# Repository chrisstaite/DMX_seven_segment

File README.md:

# DMX Seven Segment
An implementation of a DMX controller using a seven segment display
on an ATmega32A.

This utilises a small board with three buttons for up/down/channel
and a seven segment display to show the value.  A WS2812 shows the
RGB value.

All of the code is written to be run directly on the ATmega32A
without any external libraries other than AVR-Libc.

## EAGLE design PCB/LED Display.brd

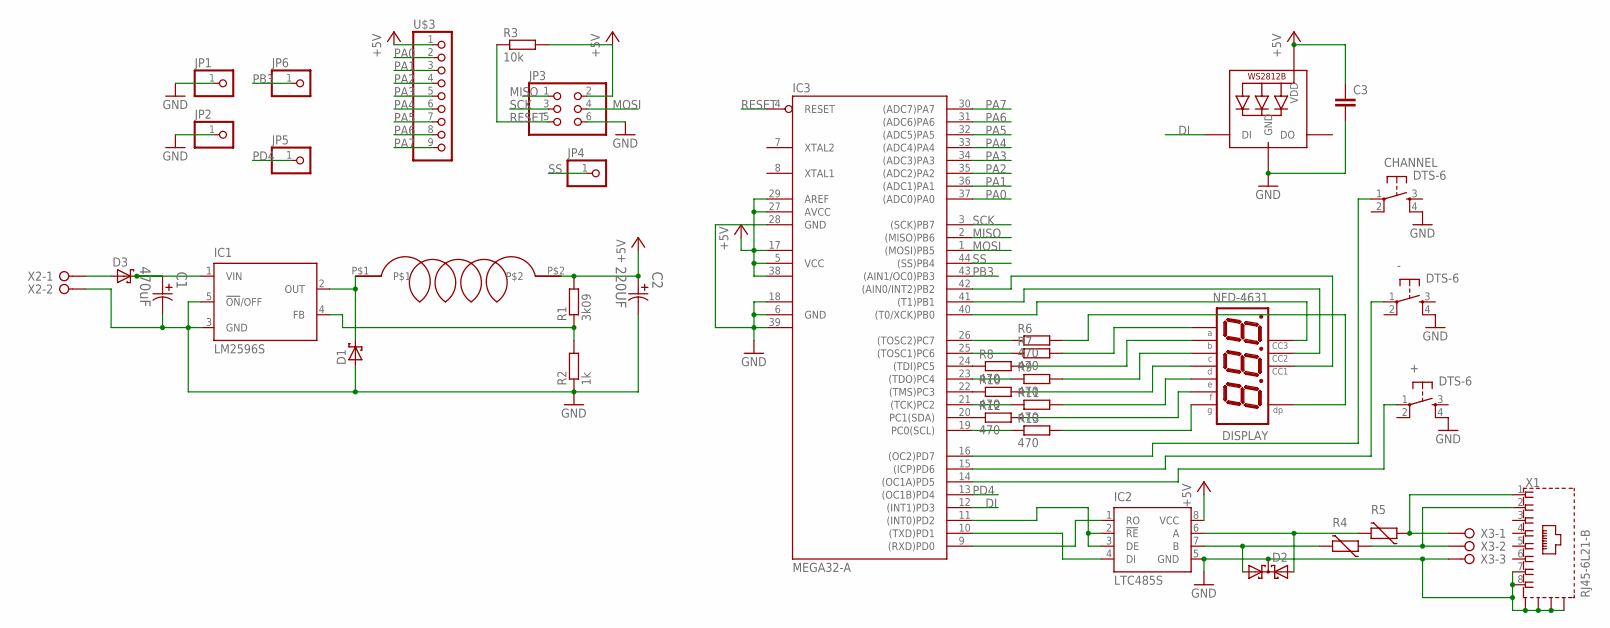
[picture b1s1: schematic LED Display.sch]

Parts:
+: DTS-6
-: DTS-6
C1: 470uF; CAPAE1030X1050N
C2: 220UF; CAPAE660X610N
C3: C-EUC0805; C0805
CHANNEL: DTS-6
D1, D3: MBRS130LT3; SMB
D2: BAS40-05; SOT23
DISPLAY: NFD-4631; NFD-5631
IC1: LM2596S; TO263-5
IC2: LTC485S; SOIC8
IC3: MEGA32-A; TQFP44
JP1, JP2, JP5, JP6: PINHD-1X1CB; 1X01-CLEANBIG
JP3: PINHD-2X3; 2X03
JP4: PINHD-1X1; 1X01
LED1: WS2812B5050; WS2812B
R1: 3k09; M0805
R2: 1k; M0805
R3: 10k; M0805
R4, R5: VARISTORCN1812; CT/CN1812; FARNELL 1652168
R6, R7, R8, R9, R10, R11, R12, R13: 470; M0805
U$1: SRN8040
U$3: PINHD-1X9; 1X09-BIG
X1: RJ45-6L21-B; RJ45-SHIELD1
X2: W237-02P; W237-132
X3: W237-03P; W237-133

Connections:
+5V: C2.1, C3.1, IC2.8 (VCC), IC3.5 (VCC), IC3.17 (VCC1), IC3.27 (AVCC), IC3.29 (AREF), IC3.38 (VCC2), JP3.2, LED1.1-VDD (VDD), R1.2, R3.2, U$1.P$2, U$3.1
DI: IC3.12 ((INT1)PD3), LED1.4-DIN (DI)
GND: +.4, -.4, C1.2, C2.2, C3.2, CHANNEL.4, D1.A, D2.3 (C), IC1.3 (GND), IC1.5 (!ON!/OFF), IC2.5 (GND), IC3.6 (GND), IC3.18 (GND1), IC3.28 (GND), IC3.39 (GND2), JP1.1, JP2.1, JP3.6, LED1.3-GND (GND), R2.1, X1.7, X1.8, X1.S1 (S), X1.S2 (S), X1.S3 (S), X1.S4 (S), X2.2, X3.3
MISO: IC3.2 ((MISO)PB6), JP3.1
MOSI: IC3.1 ((MOSI)PB5), JP3.4
unnamed: C1.1, D3.C, IC1.1 (VIN)
unnamed: D2.1 (A1), IC2.7 (B), R4.2
unnamed: IC1.4 (FB), R1.1, R2.2
unnamed: D1.C, IC1.2 (OUT), U$1.P$1
unnamed: D2.2 (A2), IC2.6 (A), R5.2
unnamed: IC2.2 (!RE), IC2.3 (DE), IC3.11 ((INT0)PD2)
unnamed: IC2.1 (RO), IC3.9 ((RXD)PD0)
unnamed: IC2.4 (DI), IC3.10 ((TXD)PD1)
unnamed: R4.1, X1.2, X3.2
unnamed: R5.1, X1.1, X3.1
unnamed: IC3.26 ((TOSC2)PC7), R6.1
unnamed: +.1, IC3.14 ((OC1A)PD5)
unnamed: DISPLAY.P$5 (P$G), R13.2
unnamed: DISPLAY.P$10 (P$F), R12.2
unnamed: DISPLAY.P$1 (P$E), R11.2
unnamed: DISPLAY.P$2 (P$D), R10.2
unnamed: DISPLAY.P$4 (P$C), R9.2
unnamed: DISPLAY.P$7 (P$B), R8.2
unnamed: DISPLAY.P$11 (P$A), R7.2
unnamed: DISPLAY.P$3 (P$DP), R6.2
unnamed: DISPLAY.P$12 (P$CC1), IC3.42 ((AIN0/INT2)PB2)
unnamed: DISPLAY.P$9 (P$CC2), IC3.41 ((T1)PB1)
unnamed: -.1, IC3.15 ((ICP)PD6)
unnamed: CHANNEL.1, IC3.16 ((OC2)PD7)
unnamed: IC3.24 ((TDI)PC5), R8.1
unnamed: IC3.22 ((TMS)PC3), R10.1
unnamed: IC3.20 (PC1(SDA)), R12.1
unnamed: IC3.19 (PC0(SCL)), R13.1
unnamed: IC3.21 ((TCK)PC2), R11.1
unnamed: IC3.23 ((TDO)PC4), R9.1
unnamed: IC3.25 ((TOSC1)PC6), R7.1
unnamed: DISPLAY.P$8 (P$CC3), IC3.40 ((T0/XCK)PB0)
unnamed: D3.A, X2.1
PA0: IC3.37 ((ADC0)PA0), U$3.2
PA1: IC3.36 ((ADC1)PA1), U$3.3
PA2: IC3.35 ((ADC2)PA2), U$3.4
PA3: IC3.34 ((ADC3)PA3), U$3.5
PA4: IC3.33 ((ADC4)PA4), U$3.6
PA5: IC3.32 ((ADC5)PA5), U$3.7
PA6: IC3.31 ((ADC6)PA6), U$3.8
PA7: IC3.30 ((ADC7)PA7), U$3.9
PB3: IC3.43 ((AIN1/OC0)PB3), JP6.1
PD4: IC3.13 ((OC1B)PD4), JP5.1
RESET: IC3.4 (RESET), JP3.5, R3.1
SCK: IC3.3 ((SCK)PB7), JP3.3
SS: IC3.44 ((SS)PB4), JP4.1

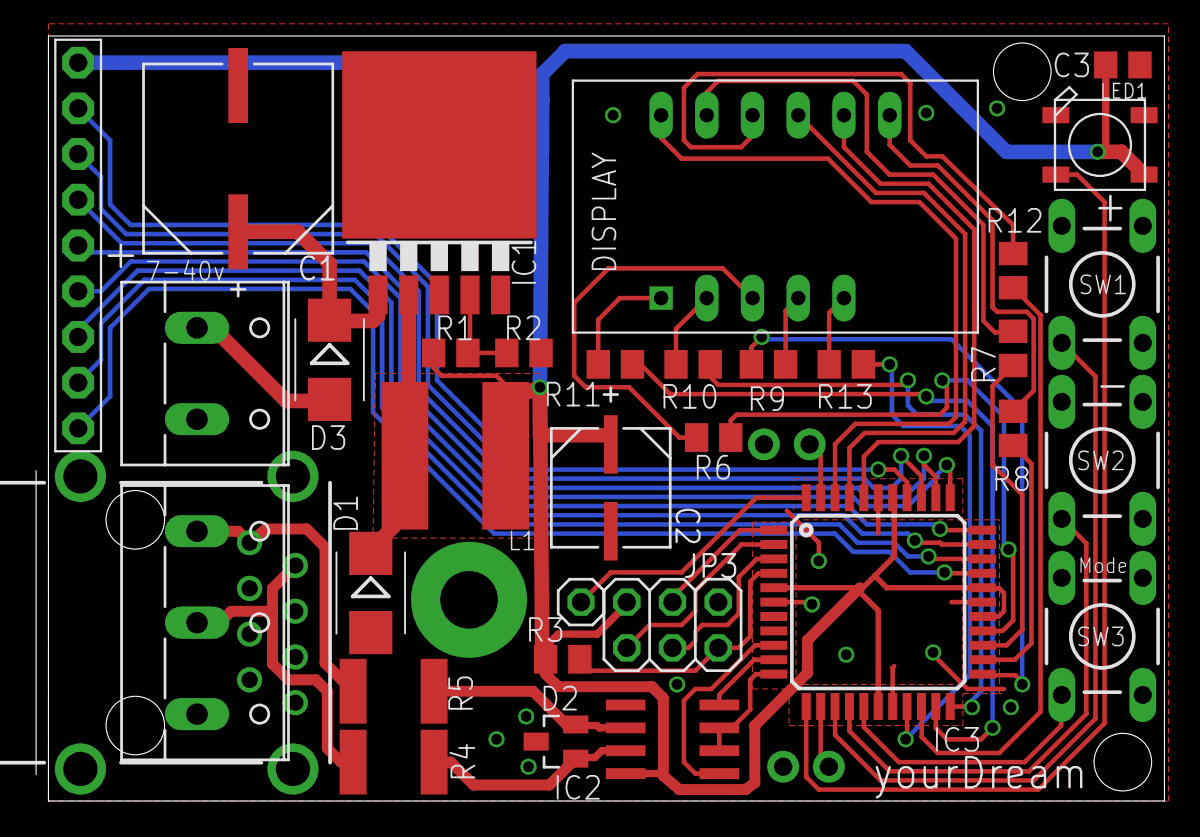
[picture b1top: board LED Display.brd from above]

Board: 2 copper layers, 62.7 x 42.5 mm, 38 parts (0 on the bottom side), 51 nets.

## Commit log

2017-02-16 Initial commit.
2017-02-16 Logic bugs fixed.
2017-02-16 Fix the DMX and WS2812 implementations.
2017-02-16 More fixes.
2017-03-05 Fixes for hardware.
2017-03-14 Display the channel on the display when changing mode.
2017-04-29 Numerous fixes.
2017-04-29 Add fuse setting to flash command.
2017-04-29 Tidy the board.
2017-05-18 Fix the orientation of the characters
